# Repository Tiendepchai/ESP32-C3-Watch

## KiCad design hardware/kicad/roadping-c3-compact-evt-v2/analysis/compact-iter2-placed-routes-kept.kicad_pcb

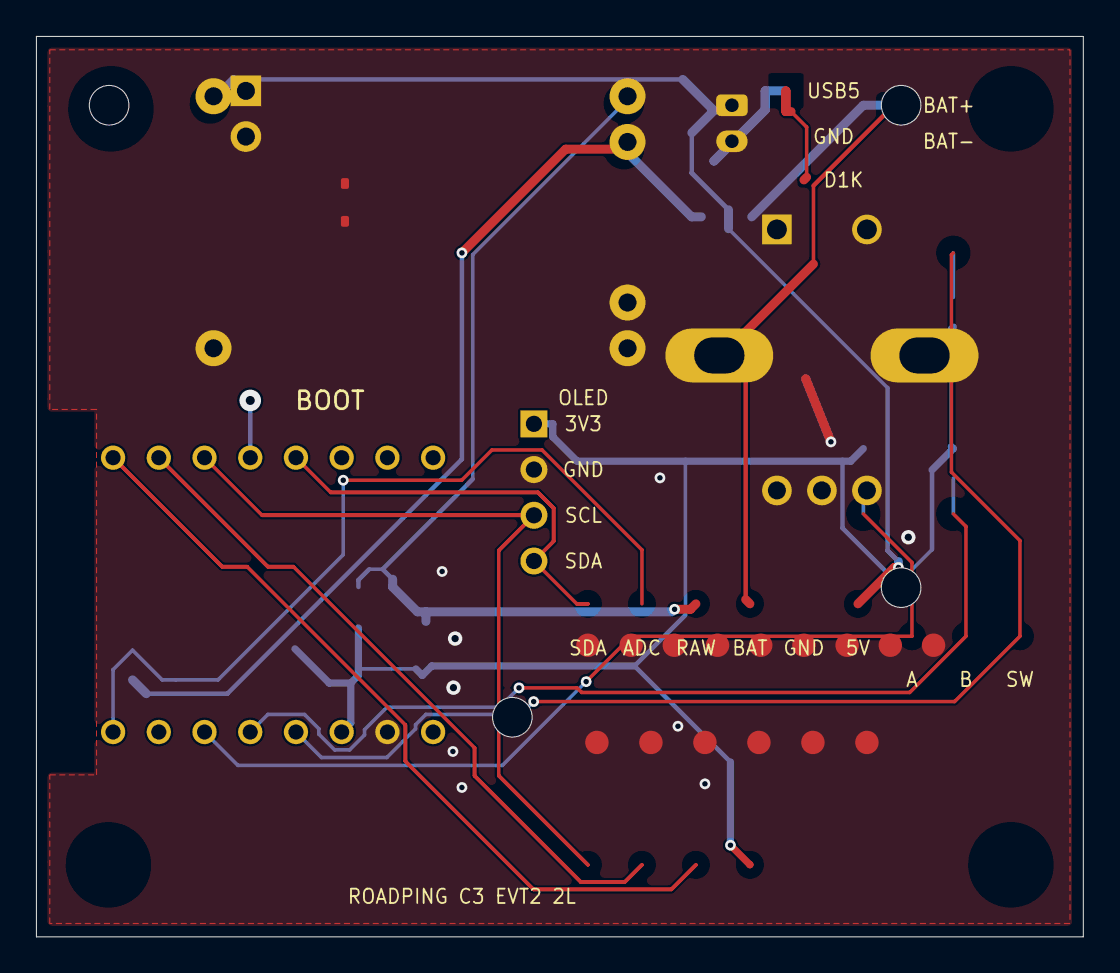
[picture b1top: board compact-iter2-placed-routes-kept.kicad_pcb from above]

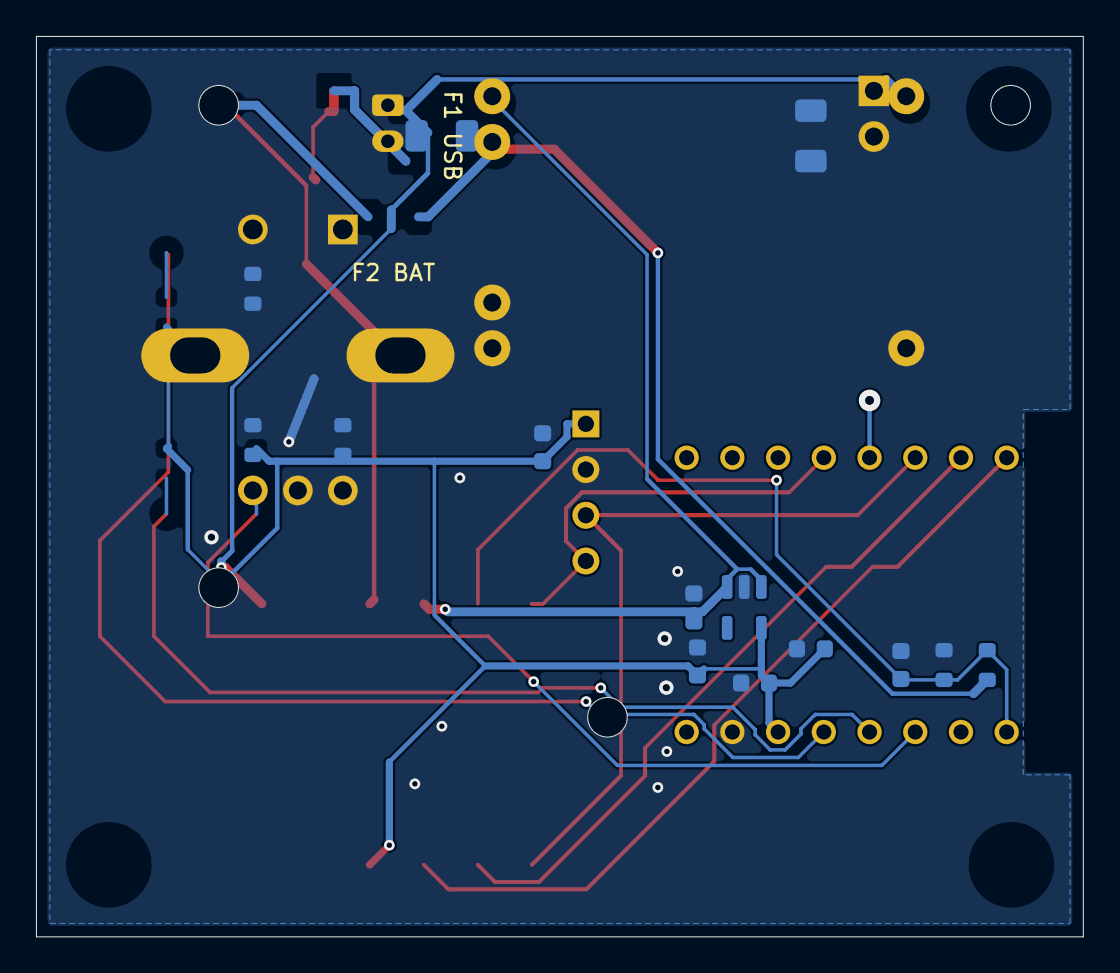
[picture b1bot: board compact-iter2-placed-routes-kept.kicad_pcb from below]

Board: 2 copper layers, 58.2 x 50.0 mm, 35 parts (14 on the bottom side), 15 nets.

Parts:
C1, C2: 1uF; C_0603_1608Metric
C3: 10uF; C_0603_1608Metric
C4, C5, C9: 100nF; C_0603_1608Metric
D1: USB_5V_TVS; D_SOD-323
DS1: SH1106_I2C_OLED; OLED_4PIN_VDD_GND_SCK_SDA_2.54MM
F1: PTC_USB_5V_1A; Fuse_1206_3216Metric
F2: PTC_BAT_1A; Fuse_1206_3216Metric
J1: USB_5V_INPUT; PinHeader_1x02_P2.54mm_Vertical
J2: JST_PH_2PIN_LIPO; JST_PH_B2B-PH-K_1x02_P2.00mm_Vertical
J3: UART_DEBUG_PROGRAM; TESTPADS_1X06_2.54MM_EVT
MH1, MH2, MH3, MH4: M2_NPTH; MountingHole_M2_NPTH_5mmKeepout
R3, R4, R5: 10k; R_0603_1608Metric
R6: 220k; R_0603_1608Metric
R7: 100k; R_0603_1608Metric
SW1: PEC11R-4215F-S0024; XDCR_PEC11R-4215F-S0024
TP1: USB_5V; TP_Round_1.0mm
TP2: BAT_CONN+; TP_Round_1.0mm
TP3: SYS_RAW; TP_Round_1.0mm
TP5: GND; TP_Round_1.0mm
TP8: I2C_SDA; TP_Round_1.0mm
TP10: ENC_A; TP_Round_1.0mm
TP11: ENC_B; TP_Round_1.0mm
TP12: ENC_SW; TP_Round_1.0mm
TP13: BAT_ADC; TP_Round_1.0mm
U1: TP4056-Module
U2: AP2112K-3.3; SOT-23-5
U3: ESP32-C3_SUPERMINI_TH; MODULE_ESP32-C3_SUPERMINI_TH

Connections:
/3V3: C2.1, C3.1, C4.1, C5.1, DS1.1 (VDD), J3.2, R3.1, R4.1, R5.1, U2.5 (VOUT), U3.3.3 (3V3)
/BAT_ADC: C9.1, R6.2, R7.1, TP13.1 (1_1), U3.0 (GPIO0)
/BAT_CONN+: F2.1, J2.1 (BAT+), TP2.1 (1_1)
/ENC_A: R3.2, SW1.A, TP10.1 (1_1), U3.2 (GPIO2)
/ENC_B: R4.2, SW1.B, TP11.1 (1_1), U3.3 (GPIO3)
/ENC_SW: R5.2, SW1.2 (SW2), TP12.1 (1_1), U3.4 (GPIO4)
/GND: C1.2, C2.2, C3.2, C4.2, C5.2, C9.2, D1.1, DS1.2 (GND), J1.2, J2.2 (BAT-), J3.1, J3.6, R7.2, SW1.1 (SW1), SW1.C, SW1.S1 (SHIELD1), SW1.S2 (SHIELD2), TP5.1 (1_1), U1.2 (IN-), U1.4 (OUT-), U1.6 (B-), U2.2 (GND), U3.G (GND)
/I2C_SCL: DS1.3 (SCK), J3.5, U3.10 (GPIO10)
/I2C_SDA: DS1.4 (SDA), TP8.1 (1_1), U3.8 (GPIO8)
/SYS_RAW: C1.1, TP3.1 (1_1), U1.3 (OUT+), U2.1 (VIN), U2.3 (EN)
/UART_RX: J3.4, U3.20 (GPIO20)
/UART_TX: J3.3, U3.21 (GPIO21)
/USB_5V: F1.2, TP1.1 (1_1), U1.1 (IN+)
/USB_5V_IN: D1.2, F1.1, J1.1
/VBAT: F2.2, R6.1, U1.5 (B+)
